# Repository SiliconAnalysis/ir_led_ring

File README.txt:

IR LED ring (ILR) illuminator
Designed to be used with Mitutoyo M Plan IR objectives

Design summary:
-ilr-ext: externally powered LED array, all in series
    ie use lab bunch supply
    r1
        scrapped due to error in inner diameter
    r2
        Shrunk ID
        Add IR warning
        Clean up mounting holes
    TODO: add fuse
    TODO: possibly increase LED hole to help set angle
-solder_jig
    Places LEDs at 45 degree angle for above assembly
-ilr-lm317: LM317 design with 12V in regulating to fixed 100 mA
    Does not work / don't use
-ilr-r: 12V in resistor limiting to around 100 mA
    Does not work / don't use

Max LED power
150 mW dissipation
100 mW current => 8 mW optical
1.4 Vdrop max => 1.4 * 0.1 = 140 - 8 mW = 132 mW
1.25 Vdrop typ => 1.25 * 0.1 = 125 - 8 mW = 117 mW
Safe to run at 100 mW continuously, assuming reasonable 25C air flow

Mityotyo M Plan APo objective measurements
Note: https://www.edmundoptics.com/microscopy/infinity-corrected-objectives/Mitutoyo-NIR-NUV-and-UV-Infinity-Corrected-Objectives/
Note: https://www.edmundoptics.com/microscopy/infinity-corrected-objectives/Mitutoyo-Infinity-Corrected-Long-Working-Distance-Objectives/
Main diameter: 32.25 mm
Objective to objective clearance on main area up to knurled area: ~30 mm
    Total clearance diameter: 32.25 + 30/2 = 47.25 mm
    Try to keep below 45
Knurled diameter: 34.00 mm
Flat area to knurled (10x objective): ~20.5 mm
Mityotyo sample working distances (note: multiple versions)
    Mag     WD
    5x      37.5
    10x     30.5
    20x     20,25.5
    50x     10,17
    100x    10,12

Dimension proposals
LEDs at 50 mm diameter
LEDs are 8.6 mm high => 10 mm approximately with standoff
Middle of PCB cut to 33 mm (touch up with file if necessary)

45 degree angle seems good starting point
What would focal point be at?
distance = 25 * sin(45) = 17.7 mm
limits use to the 20x objective

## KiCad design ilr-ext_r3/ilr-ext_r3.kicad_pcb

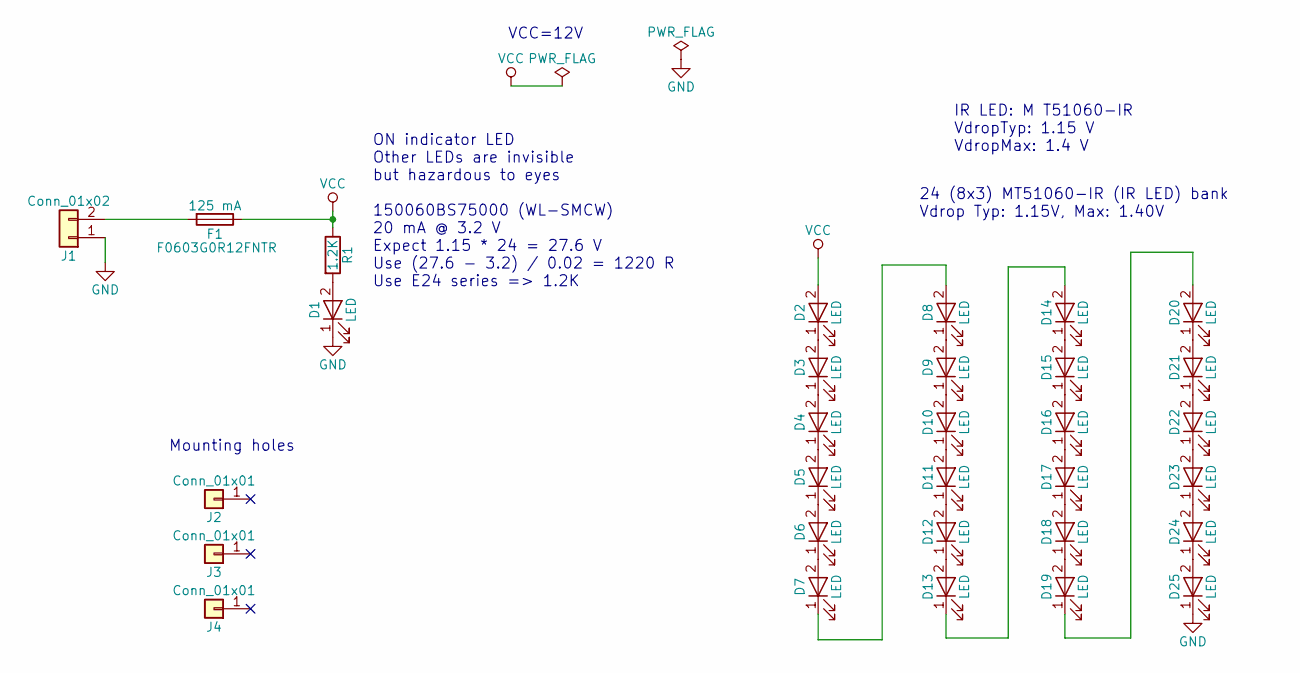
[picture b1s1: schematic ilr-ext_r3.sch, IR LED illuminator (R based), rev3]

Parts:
D1: LED; LED_0603
D2, D3, D4, D5, D6, D7, D8, D9, D10, D11, D12, D13, D14, D15, D16, D17, D18, D19, D20, D21, D22, D23, D24, D25: LED; LED_D5.0mm
F1: 125 mA; R_0603
J1: Conn_01x02; Pin_Header_Straight_1x02_Pitch2.54mm
J2, J3, J4: Conn_01x01; MountingHole_3.5mm
R1: 1.2K; R_0603

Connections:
GND: D1.1 (K), D25.1 (K), J1.1
unnamed: D1.2 (A), R1.2
unnamed: D2.1 (K), D3.2 (A)
unnamed: D3.1 (K), D4.2 (A)
unnamed: D4.1 (K), D5.2 (A)
unnamed: D5.1 (K), D6.2 (A)
unnamed: D6.1 (K), D7.2 (A)
unnamed: D7.1 (K), D8.2 (A)
unnamed: D8.1 (K), D9.2 (A)
unnamed: D10.1 (K), D11.2 (A)
unnamed: D9.1 (K), D10.2 (A)
unnamed: D11.1 (K), D12.2 (A)
unnamed: D12.1 (K), D13.2 (A)
unnamed: D13.1 (K), D14.2 (A)
unnamed: D14.1 (K), D15.2 (A)
unnamed: D15.1 (K), D16.2 (A)
unnamed: D16.1 (K), D17.2 (A)
unnamed: D17.1 (K), D18.2 (A)
unnamed: D18.1 (K), D19.2 (A)
unnamed: D19.1 (K), D20.2 (A)
unnamed: D20.1 (K), D21.2 (A)
unnamed: D21.1 (K), D22.2 (A)
unnamed: D22.1 (K), D23.2 (A)
unnamed: D23.1 (K), D24.2 (A)
unnamed: D24.1 (K), D25.2 (A)
unnamed: F1.2, J1.2
VCC: D2.2 (A), F1.1, R1.1

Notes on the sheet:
ON indicator LED Other LEDs are invisible but hazardous to eyes 150060BS75000 (WL-SMCW) 20 mA @ 3.2 V Expect 1.15 * 24 = 27.6 V Use (27.6 - 3.2) / 0.02 = 1220 R Use E24 series => 1.2K
24 (8x3) MT51060-IR (IR LED) bank Vdrop Typ: 1.15V, Max: 1.40V
VCC=12V
IR LED: M T51060-IR VdropTyp: 1.15 V VdropMax: 1.4 V
Mounting holes

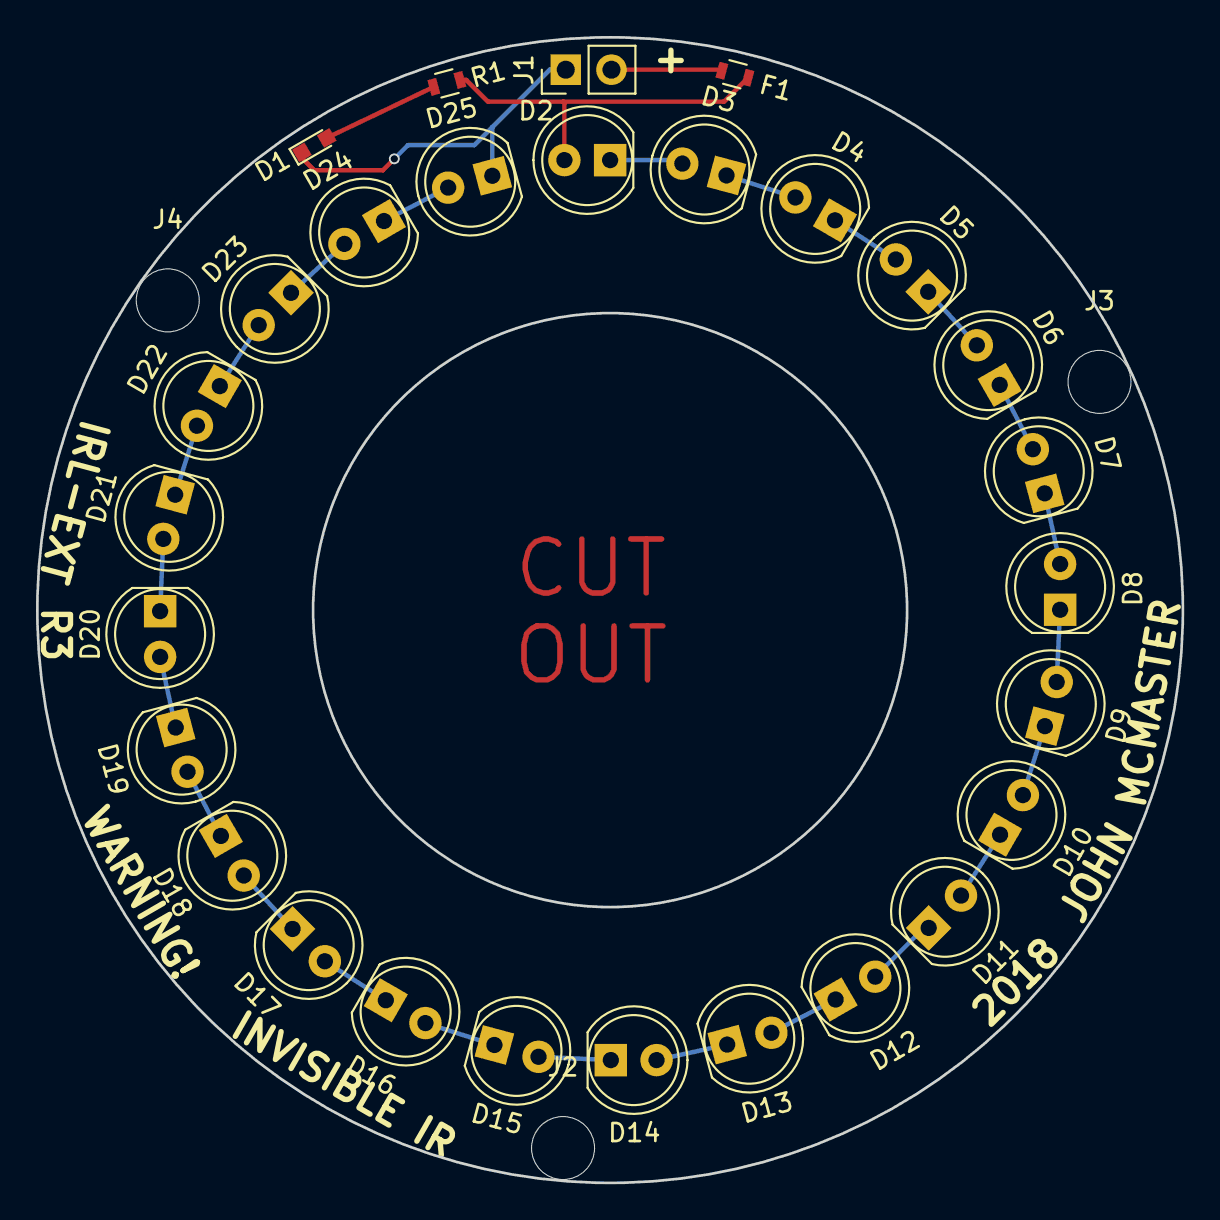
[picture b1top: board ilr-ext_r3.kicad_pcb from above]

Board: 2 copper layers, 63.6 x 63.6 mm, 31 parts (0 on the bottom side), 27 nets.

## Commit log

2018-05-21 Illuminator schematic (LM317 based)
2018-05-21 Illuminator schematic (R based)
2018-05-21 README + gitignore
2018-05-21 Add datasheets
2018-05-23 sync
2018-06-13 sync files
2018-06-16 ilr-ext_r3: future build tweaks
2018-06-16 fuse datasheet
